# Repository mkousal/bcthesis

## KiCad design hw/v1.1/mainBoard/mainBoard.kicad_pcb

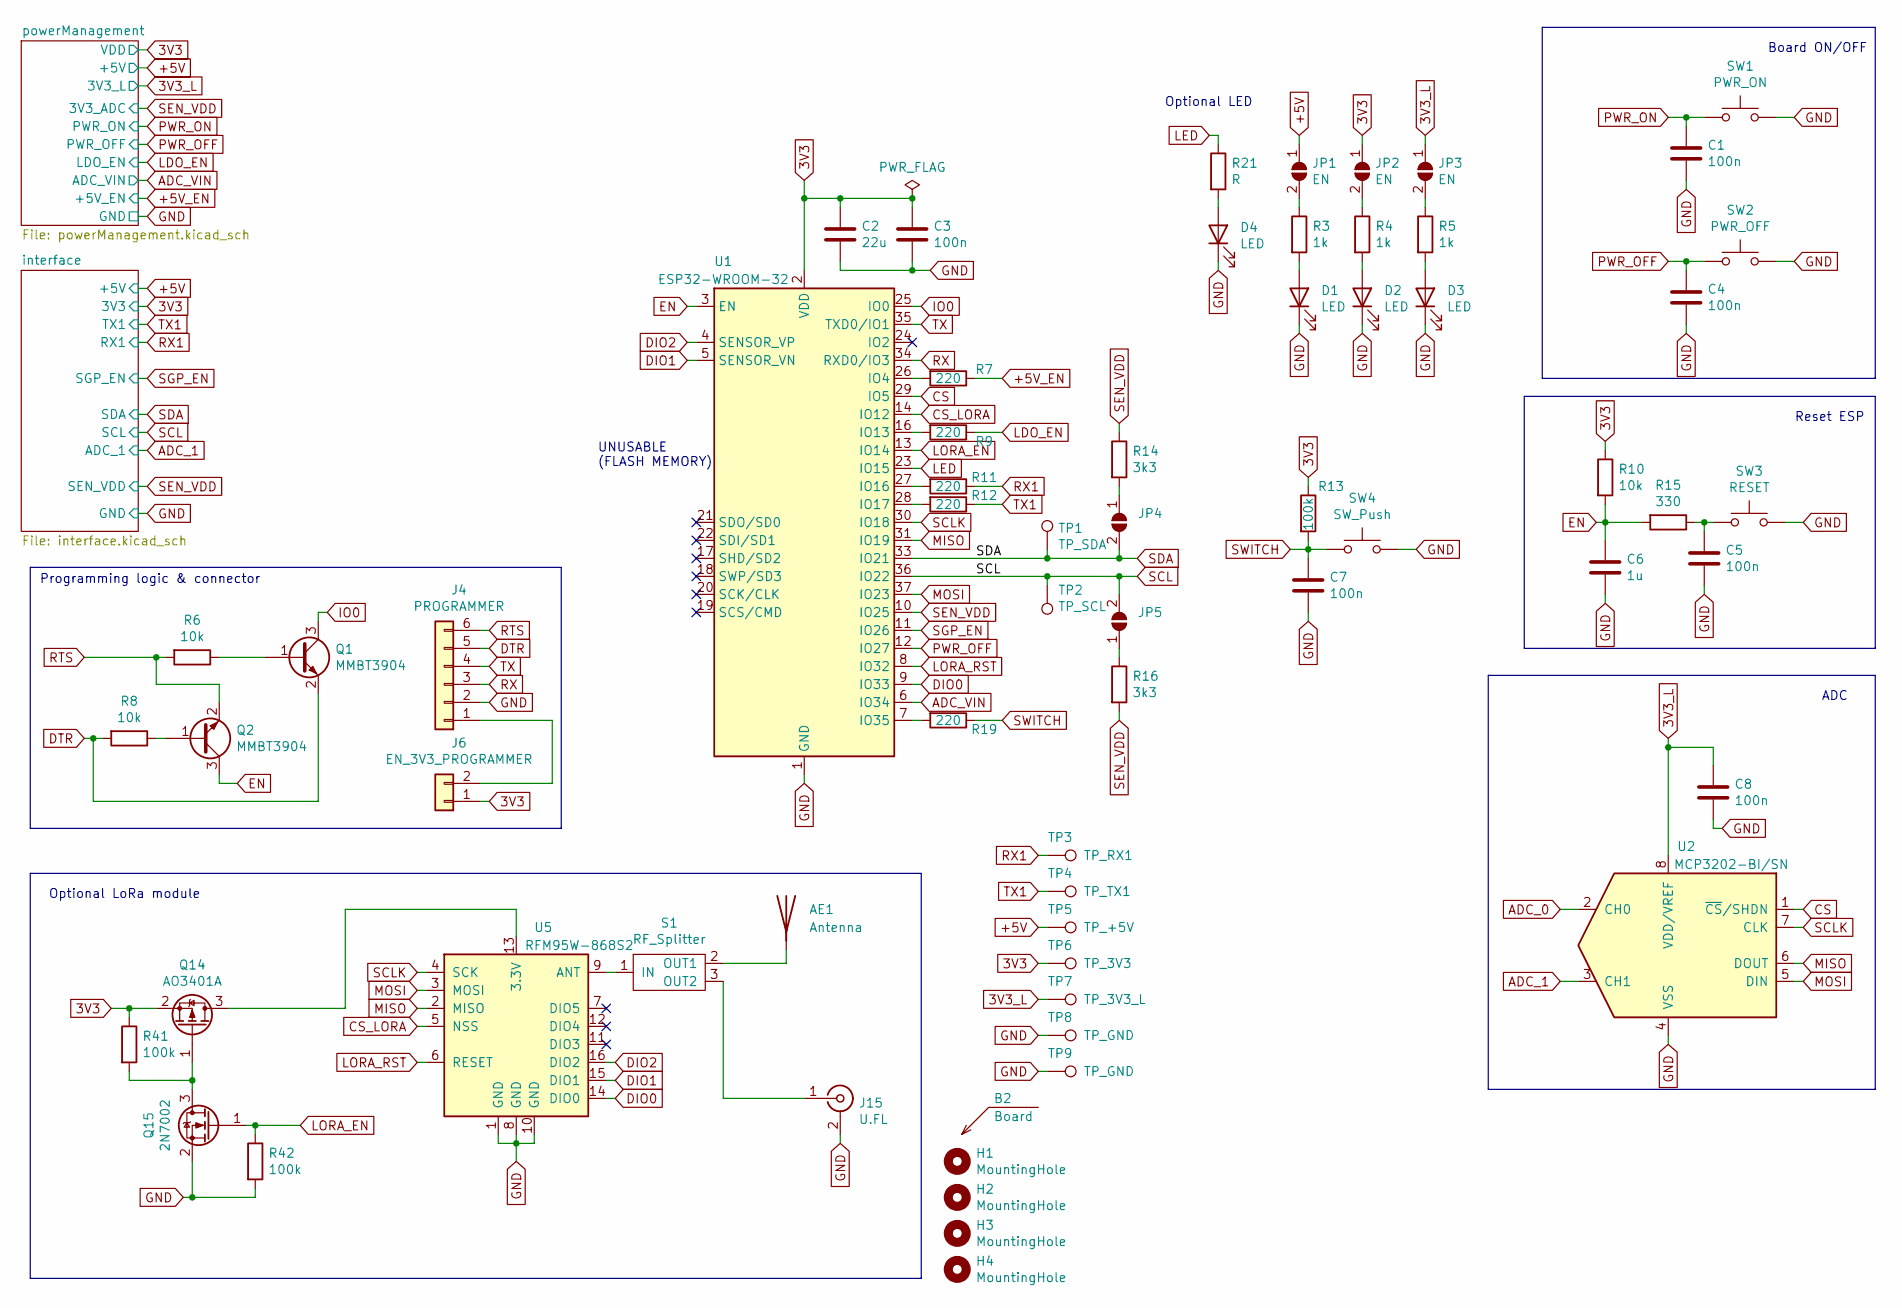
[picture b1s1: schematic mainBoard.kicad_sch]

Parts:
AE1: Antenna; ANT-868-CHP-T
B2: Board
C1, C3, C4, C5, C7, C8: 100n; C_0603_1608Metric; LCSC C1525
C2: 22u; C_0805_2012Metric; LCSC C45783
C6: 1u; C_0805_2012Metric; LCSC C52923
D1, D2, D3, D4: LED; LED_0805_2012Metric_Pad1.15x1.40mm_HandSolder
H1, H2, H3, H4: MountingHole; MountingHole_3.2mm_M3_Pad_Via
J4: PROGRAMMER; PinHeader_1x06_P2.54mm_Vertical
J6: EN_3V3_PROGRAMMER; PinHeader_1x02_P2.54mm_Vertical
J15: U.FL; U.FL_Hirose_U.FL-R-SMT-1_Vertical
JP1, JP2, JP3: EN; SolderJumper-2_P1.3mm_Open_RoundedPad1.0x1.5mm
JP4, JP5: SolderJumper-2_P1.3mm_Open_TrianglePad1.0x1.5mm
Q1, Q2: MMBT3904; SOT-23; LCSC C20526
Q14: AO3401A; SOT-23; LCSC C15127
Q15: 2N7002; SOT-23; LCSC C8545
R3, R4, R5: 1k; R_0805_2012Metric; LCSC C11702
R6, R8, R10: 10k; R_0805_2012Metric; LCSC C25744
R7, R9, R11, R12, R19: 220; R_0805_2012Metric; LCSC C25091
R13, R41, R42: 100k; R_0805_2012Metric; LCSC C25741
R14, R16: 3k3; R_0805_2012Metric; LCSC C25890
R15: 330; R_0805_2012Metric; LCSC C25104
R21: R; R_0805_2012Metric
S1: RF_Splitter
SW1: PWR_ON; SW_PUSH_6mm
SW2: PWR_OFF; SW_PUSH_6mm
SW3: RESET; SW_PUSH_6mm
SW4: SW_Push; SW_PUSH_6mm
TP1: TP_SDA; TestPoint_Pad_D1.5mm
TP2: TP_SCL; TestPoint_Pad_D1.5mm
TP3: TP_RX1; TestPoint_Pad_D1.5mm
TP4: TP_TX1; TestPoint_Pad_D1.5mm
TP5: TP_+5V; TestPoint_Pad_D1.5mm
TP6: TP_3V3; TestPoint_Pad_D1.5mm
TP7: TP_3V3_L; TestPoint_Pad_D1.5mm
TP8, TP9: TP_GND; TestPoint_Pad_D1.5mm
U1: ESP32-WROOM-32; LCSC C82899
U2: MCP3202-BI/SN; SOIC-8_3.9x4.9mm_P1.27mm
U5: RFM95W-868S2; HOPERF_RFM9XW_SMD

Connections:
3V3: C2.1, C3.1, J6.1, JP2.1 (A), Q14.2 (S), R10.1, R13.1, R41.1, TP6.1, U1.2 (VDD); also elsewhere on the board
3V3_L: C8.1, JP3.1 (A), TP7.1, U2.8 (VDD/VREF); also elsewhere on the board
+5V: JP1.1 (A), TP5.1; also elsewhere on the board
+5V_EN: R7.1; also elsewhere on the board
ADC_0: U2.2 (CH0)
ADC_1: U2.3 (CH1); also elsewhere on the board
ADC_VIN: U1.6 (IO34); also elsewhere on the board
CS: U1.29 (IO5), U2.1 (~CS/SHDN)
CS_LORA: U1.14 (IO12), U5.5 (NSS)
DIO0: U1.9 (IO33), U5.14 (DIO0)
DIO1: U1.5 (SENSOR_VN), U5.15 (DIO1)
DIO2: U1.4 (SENSOR_VP), U5.16 (DIO2)
DTR: J4.5, Q1.2 (E), R8.2
EN: C6.1, Q2.3 (C), R10.2, R15.2, U1.3 (EN)
GND: C1.2, C2.2, C3.2, C4.2, C5.2, C6.2, C7.2, C8.2, D1.1 (K), D2.1 (K), D3.1 (K), D4.1 (K), J4.2, J15.2 (Ext), Q15.2 (S), R42.2, SW1.2, SW2.2, SW3.2, SW4.2, TP8.1, TP9.1, U1.1 (GND), U1.15 (GND), U1.38 (GND), U1.39 (GND), U2.4 (VSS), U5.1 (GND), U5.8 (GND), U5.10 (GND); also elsewhere on the board
IO0: Q1.3 (C), U1.25 (IO0)
LDO_EN: R9.1; also elsewhere on the board
LED: R21.1, U1.23 (IO15)
LORA_EN: Q15.1 (G), R42.1, U1.13 (IO14)
LORA_RST: U1.8 (IO32), U5.6 (RESET)
MISO: U1.31 (IO19), U2.6 (DOUT), U5.2 (MISO)
MOSI: U1.37 (IO23), U2.5 (DIN), U5.3 (MOSI)
unnamed: AE1.1 (A), S1.2 (OUT1)
unnamed: C5.1, R15.1, SW3.1
unnamed: D1.2 (A), R3.2
unnamed: D2.2 (A), R4.2
unnamed: D3.2 (A), R5.2
unnamed: D4.2 (A), R21.2
unnamed: J4.1, J6.2
unnamed: J15.1 (In), S1.3 (OUT2)
unnamed: JP1.2 (B), R3.1
unnamed: JP2.2 (B), R4.1
unnamed: JP3.2 (B), R5.1
unnamed: JP4.1 (A), R14.2
unnamed: JP5.1 (A), R16.1
unnamed: Q1.1 (B), R6.1
unnamed: Q2.1 (B), R8.1
unnamed: Q14.1 (G), Q15.3 (D), R41.2
unnamed: Q14.3 (D), U5.13 (3.3V)
unnamed: R7.2, U1.26 (IO4)
unnamed: R9.2, U1.16 (IO13)
unnamed: R11.2, U1.27 (IO16)
unnamed: R12.2, U1.28 (IO17)
unnamed: R19.2, U1.7 (IO35)
unnamed: S1.1 (IN), U5.9 (ANT)
PWR_OFF: C4.1, SW2.1, U1.12 (IO27); also elsewhere on the board
PWR_ON: C1.1, SW1.1; also elsewhere on the board
RTS: J4.6, Q2.2 (E), R6.2
RX: J4.3, U1.34 (RXD0/IO3)
RX1: R11.1, TP3.1; also elsewhere on the board
SCL: JP5.2 (B), TP2.1, U1.36 (IO22); also elsewhere on the board
SCLK: U1.30 (IO18), U2.7 (CLK), U5.4 (SCK)
SDA: JP4.2 (B), TP1.1, U1.33 (IO21); also elsewhere on the board
SEN_VDD: R14.1, R16.2, U1.10 (IO25); also elsewhere on the board
SGP_EN: U1.11 (IO26); also elsewhere on the board
SWITCH: C7.1, R13.2, R19.1, SW4.1
TX: J4.4, U1.35 (TXD0/IO1)
TX1: R12.1, TP4.1; also elsewhere on the board

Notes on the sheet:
ADC
Programming logic & connector
Reset ESP
Optional LoRa module
UNUSABLE (FLASH MEMORY)
Board ON/OFF
Optional LED

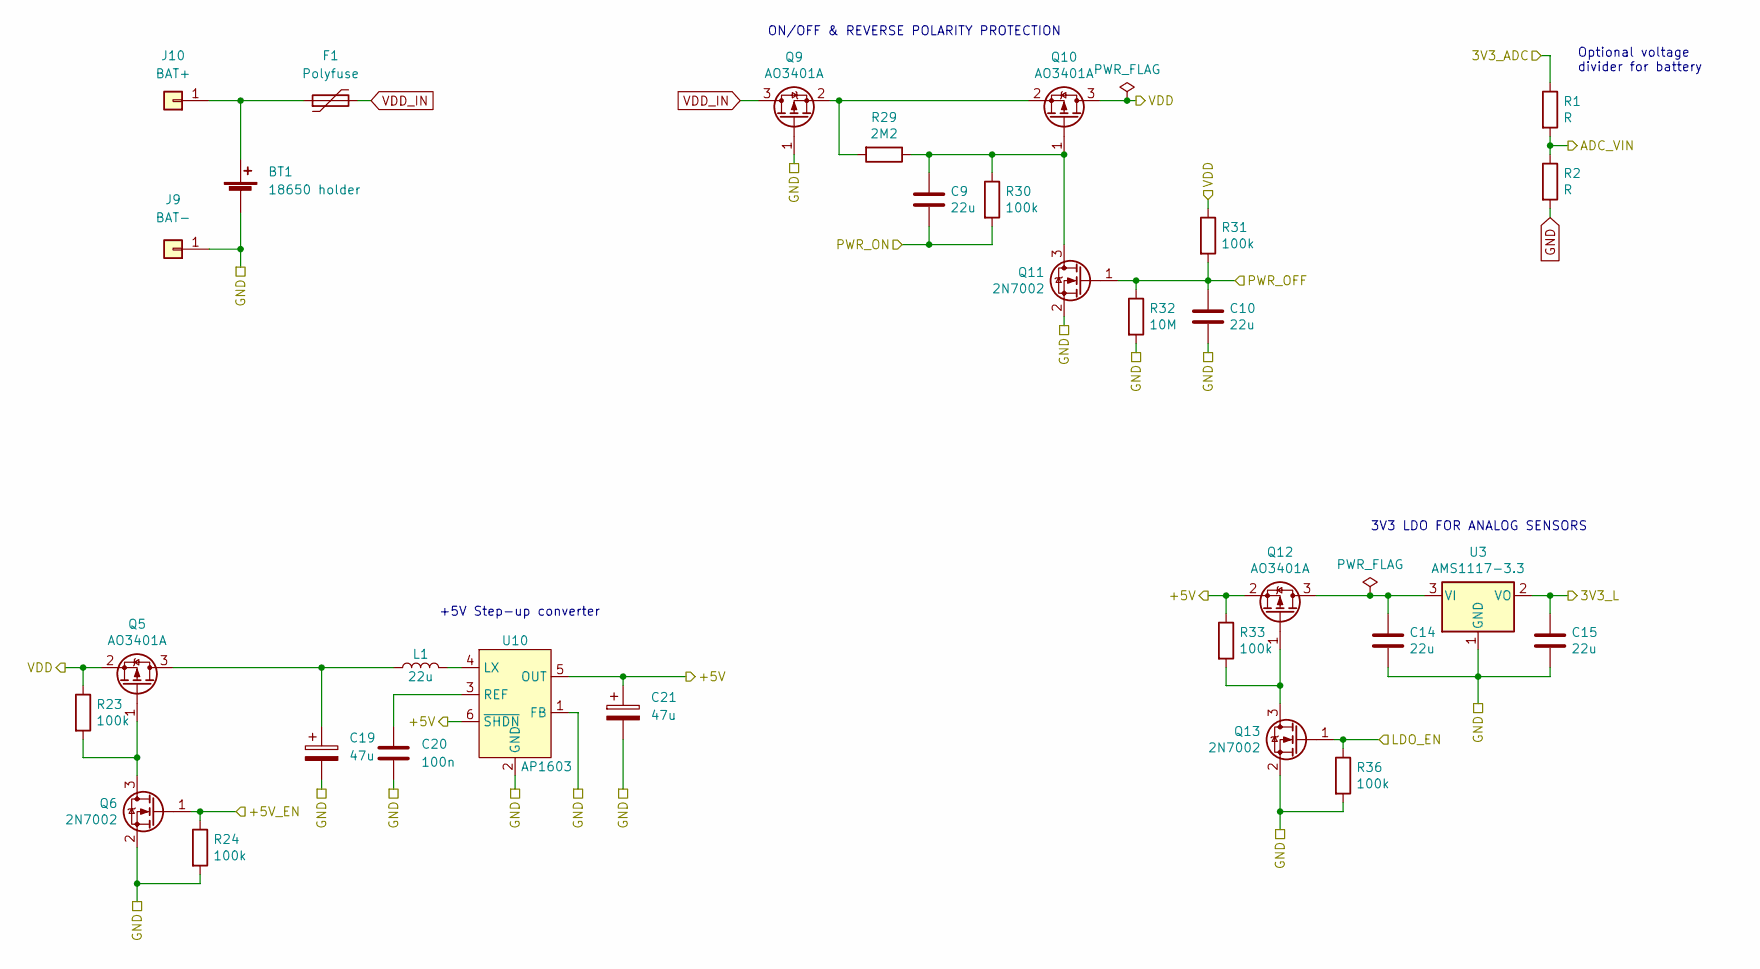
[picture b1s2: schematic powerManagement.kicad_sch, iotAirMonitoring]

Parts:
BT1: 18650 holder; JST_XH_B2B-XH-A_1x02_P2.50mm_Vertical
C9, C10, C14, C15: 22u; C_0805_2012Metric; LCSC C45783
C19, C21: 47u; CP_Elec_6.3x7.7
C20: 100n; C_0603_1608Metric
F1: Polyfuse; Fuse_1812_4532Metric_Pad1.30x3.40mm_HandSolder
J9: BAT-; 2mm_Banana-Socket
J10: BAT+; 2mm_Banana-Socket
L1: 22u; L_Coilcraft_LPS4018
Q5, Q9, Q10, Q12: AO3401A; SOT-23; LCSC C15127
Q6, Q11, Q13: 2N7002; SOT-23; LCSC C8545
R1, R2: R; R_0805_2012Metric_Pad1.20x1.40mm_HandSolder
R23, R24, R30, R33, R36: 100k; R_0805_2012Metric; LCSC C25741
R29: 2M2; R_0805_2012Metric; LCSC C25741
R31: 100k; R_0805_2012Metric; LCSC C25744
R32: 10M; R_0805_2012Metric; LCSC C25741
U3: AMS1117-3.3; SOT-223-3_TabPin2; LCSC C6186
U10: AP1603; SOT-23-6_Handsoldering

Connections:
3V3: Q5.2 (S), Q10.3 (D), R23.1, R31.1; also elsewhere on the board
3V3_L: C15.1, U3.2 (VO); also elsewhere on the board
+5V: C21.1, Q12.2 (S), R33.1, U10.5 (OUT), U10.6 (~SHDN); also elsewhere on the board
+5V_EN: Q6.1 (G), R24.1; also elsewhere on the board
ADC_VIN: R1.2, R2.1; also elsewhere on the board
GND: BT1.2 (-), C10.2, C14.2, C15.2, C19.2, C20.2, C21.2, J9.1, Q6.2 (S), Q9.1 (G), Q11.2 (S), Q13.2 (S), R2.2, R24.2, R32.2, R36.2, U3.1 (GND), U10.1 (FB), U10.2 (GND); also elsewhere on the board
LDO_EN: Q13.1 (G), R36.1; also elsewhere on the board
unnamed: BT1.1 (+), F1.1, J10.1
unnamed: C9.1, Q10.1 (G), Q11.3 (D), R29.1, R30.1
unnamed: C14.1, Q12.3 (D), U3.3 (VI)
unnamed: C19.1, L1.1, Q5.3 (D)
unnamed: C20.1, U10.3 (REF)
unnamed: L1.2, U10.4 (LX)
unnamed: Q5.1 (G), Q6.3 (D), R23.2
unnamed: Q9.2 (S), Q10.2 (S), R29.2
unnamed: Q12.1 (G), Q13.3 (D), R33.2
PWR_OFF: C10.1, Q11.1 (G), R31.2, R32.1; also elsewhere on the board
PWR_ON: C9.2, R30.2; also elsewhere on the board
SEN_VDD: R1.1; also elsewhere on the board
VDD_IN: F1.2, Q9.3 (D)

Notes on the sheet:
Optional voltage divider for battery
+5V Step-up converter
ON/OFF & REVERSE POLARITY PROTECTION
3V3 LDO FOR ANALOG SENSORS

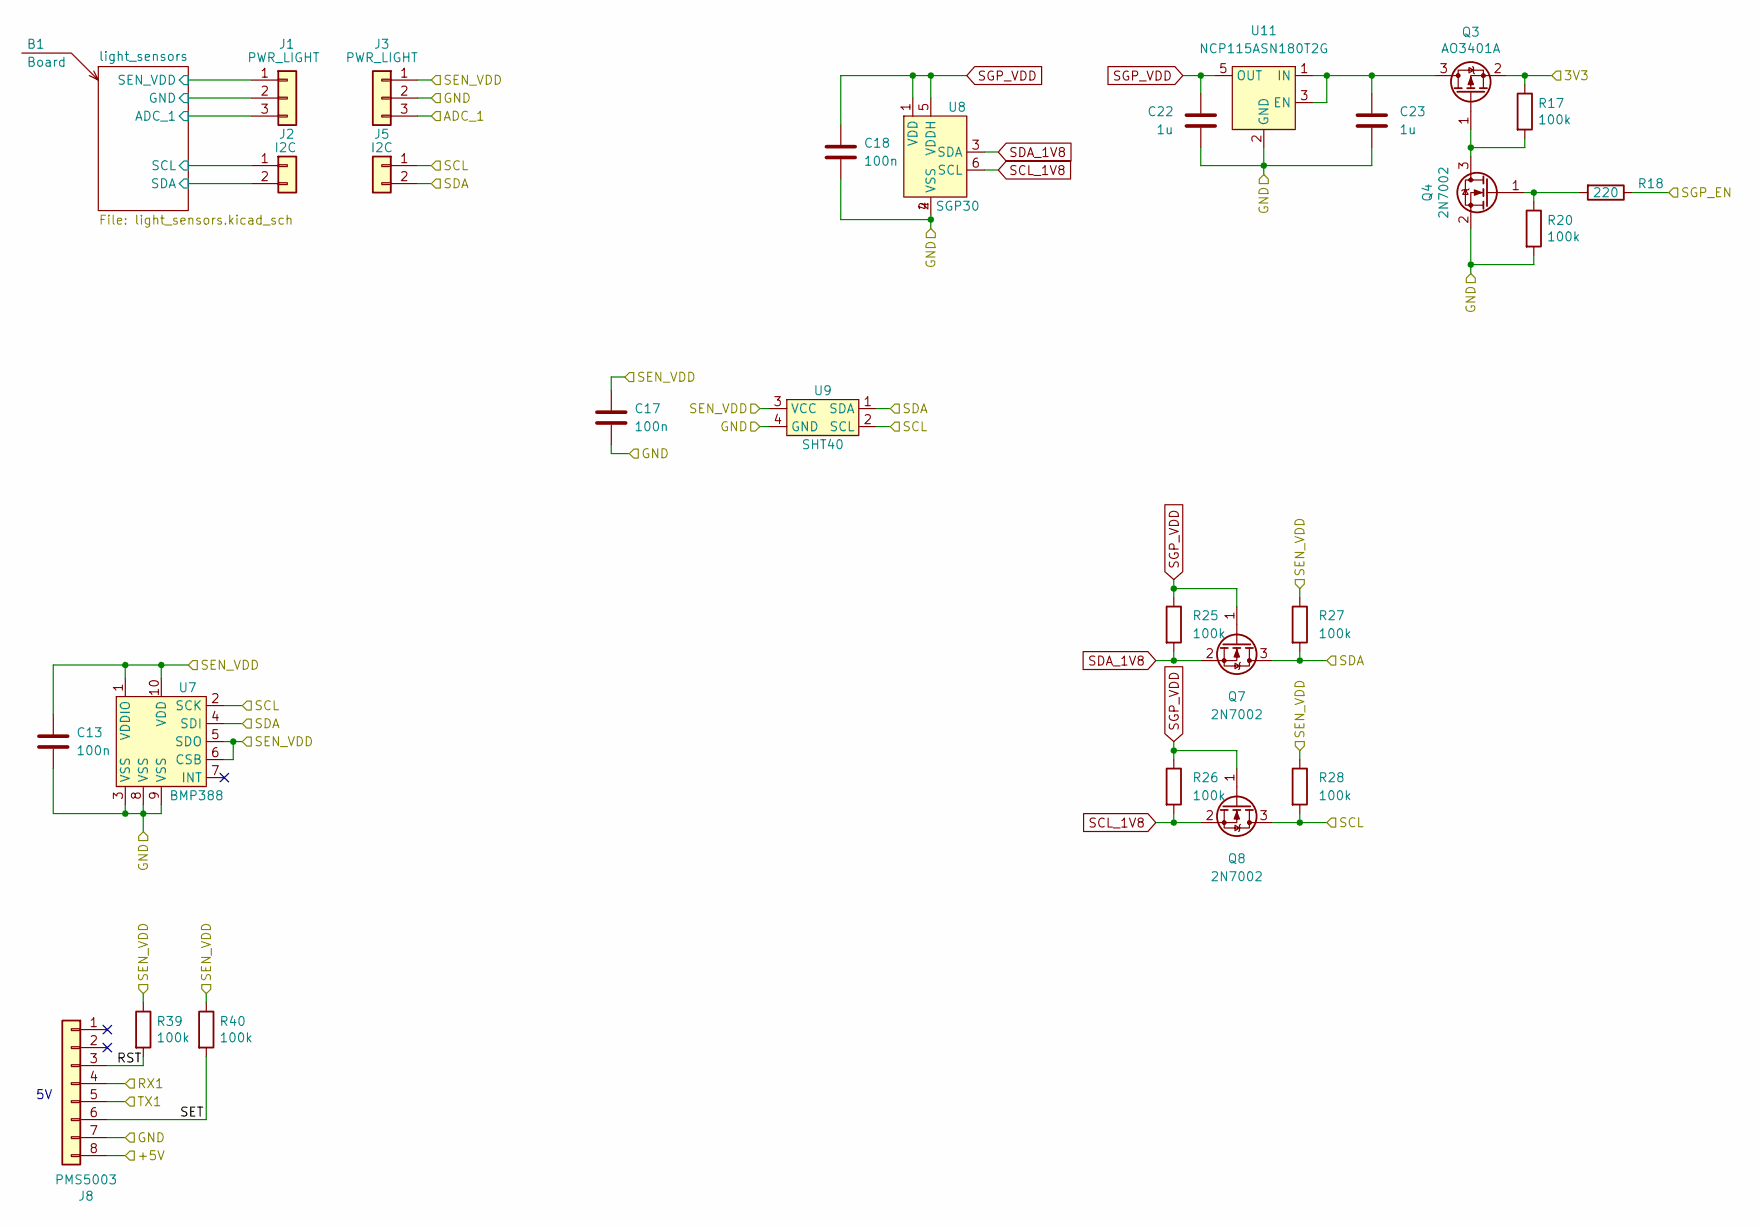
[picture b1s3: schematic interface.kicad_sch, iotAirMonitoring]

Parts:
B1: Board
C13, C17, C18: 100n; C_0603_1608Metric
C22, C23: 1u; C_0805_2012Metric
J1: PWR_LIGHT; PinHeader_1x03_P2.54mm_Vertical
J2: I2C; PinHeader_1x02_P2.54mm_Vertical
J3: PWR_LIGHT; PinSocket_1x03_P2.54mm_Vertical
J5: I2C; PinSocket_1x02_P2.54mm_Vertical
J8: PMS5003; Molex_PicoBlade_53048-0810_1x08_P1.25mm_Horizontal
Q3: AO3401A; SOT-23; LCSC C15127
Q4: 2N7002; SOT-23; LCSC C8545
Q7, Q8: 2N7002; SOT-23
R17, R20, R39, R40: 100k; R_0805_2012Metric; LCSC C25741
R18: 220; R_0805_2012Metric; LCSC C25091
R25, R26, R27, R28: 100k; R_0805_2012Metric
U7: BMP388
U8: SGP30
U9: SHT40
U11: NCP115ASN180T2G; TSOP-5_1.65x3.05mm_P0.95mm

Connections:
3V3: Q3.2 (S), R17.1; also elsewhere on the board
+5V: J8.8; also elsewhere on the board
/interface/RST: J8.3, R39.2
/interface/SET: J8.6, R40.2
/interface/light_sensors/ADC_1: J1.3; also elsewhere on the board
/interface/light_sensors/GND: J1.2; also elsewhere on the board
/interface/light_sensors/SCL: J2.1; also elsewhere on the board
/interface/light_sensors/SDA: J2.2; also elsewhere on the board
/interface/light_sensors/SEN_VDD: J1.1; also elsewhere on the board
ADC_1: J3.3; also elsewhere on the board
GND: C13.2, C17.2, C18.2, C22.2, C23.2, J3.2, J8.7, Q4.2 (S), R20.2, U7.3 (VSS), U7.8 (VSS), U7.9 (VSS), U8.2 (VSS), U8.4, U9.4 (GND), U11.2 (GND); also elsewhere on the board
unnamed: C23.1, Q3.3 (D), U11.1 (IN), U11.3 (EN)
unnamed: Q3.1 (G), Q4.3 (D), R17.2
unnamed: Q4.1 (G), R18.2, R20.1
RX1: J8.4; also elsewhere on the board
SCL: J5.1, Q8.3 (D), R28.2, U7.2 (SCK), U9.2 (SCL); also elsewhere on the board
SCL_1V8: Q8.2 (S), R26.2, U8.6 (SCL)
SDA: J5.2, Q7.3 (D), R27.2, U7.4 (SDI), U9.1 (SDA); also elsewhere on the board
SDA_1V8: Q7.2 (S), R25.2, U8.3 (SDA)
SEN_VDD: C13.1, C17.1, J3.1, R27.1, R28.1, R39.1, R40.1, U7.1 (VDDIO), U7.5 (SDO), U7.6 (CSB), U7.10 (VDD), U9.3 (VCC); also elsewhere on the board
SGP_EN: R18.1; also elsewhere on the board
SGP_VDD: C18.1, C22.1, Q7.1 (G), Q8.1 (G), R25.1, R26.1, U8.1 (VDD), U8.5 (VDDH), U11.5 (OUT)
TX1: J8.5; also elsewhere on the board

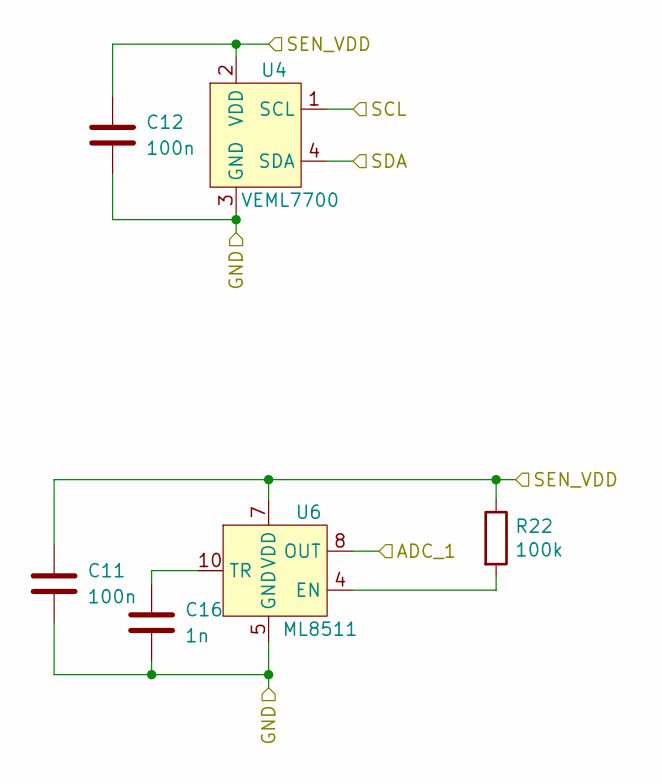
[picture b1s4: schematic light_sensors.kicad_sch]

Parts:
C11, C12: 100n; C_0603_1608Metric
C16: 1n; C_0805_2012Metric
R22: 100k; R_0805_2012Metric; LCSC C25741
U4: VEML7700
U6: ML8511

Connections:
/interface/light_sensors/ADC_1: U6.8 (OUT); also elsewhere on the board
/interface/light_sensors/GND: C11.2, C12.2, C16.2, U4.3 (GND), U6.5 (GND); also elsewhere on the board
/interface/light_sensors/SCL: U4.1 (SCL); also elsewhere on the board
/interface/light_sensors/SDA: U4.4 (SDA); also elsewhere on the board
/interface/light_sensors/SEN_VDD: C11.1, C12.1, R22.1, U4.2 (VDD), U6.7 (VDD); also elsewhere on the board
unnamed: C16.1, U6.10 (TR)
unnamed: R22.2, U6.4 (EN)

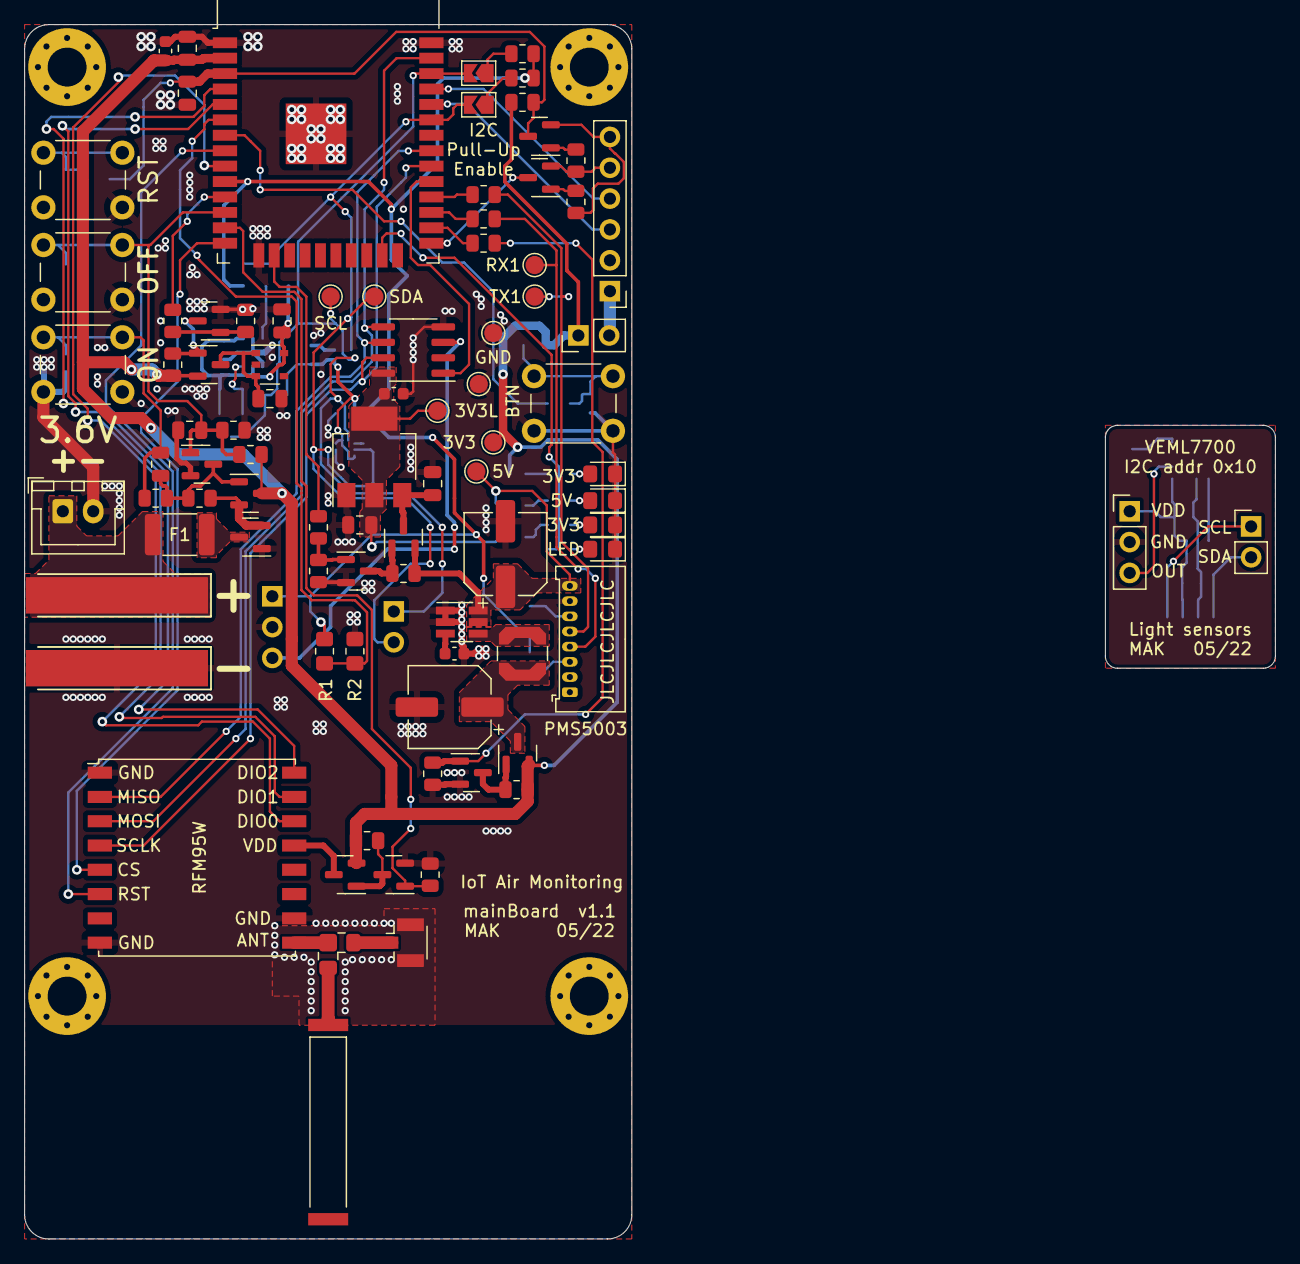
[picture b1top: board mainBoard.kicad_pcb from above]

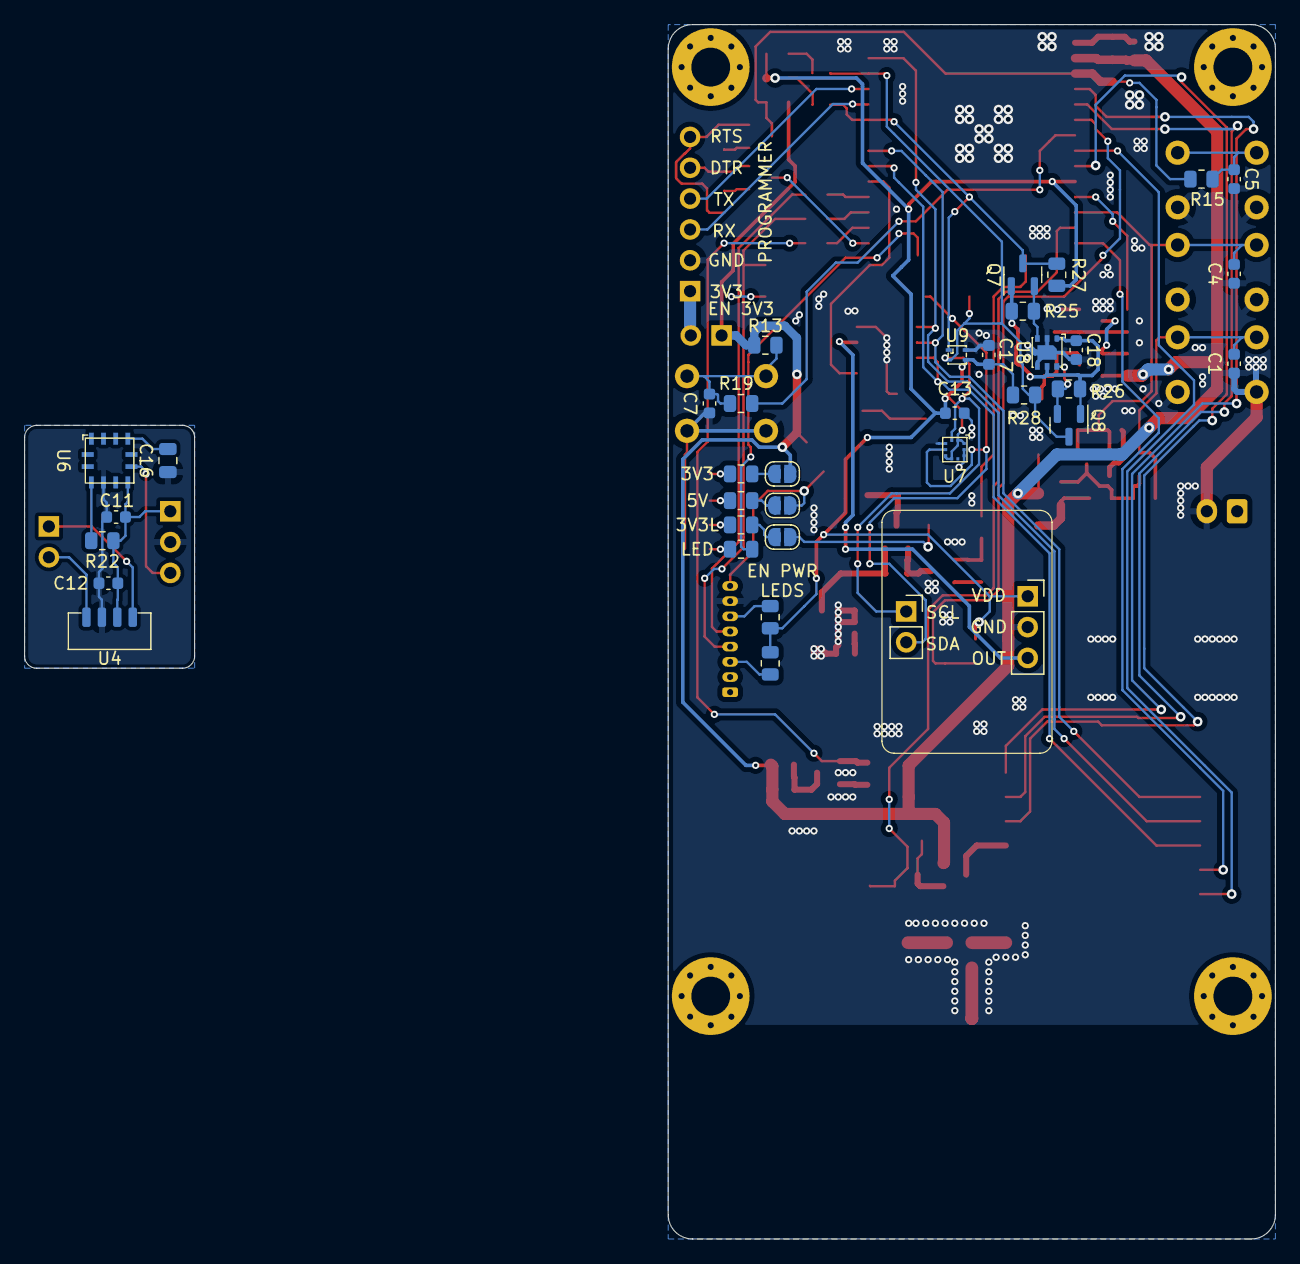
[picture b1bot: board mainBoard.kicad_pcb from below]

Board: 2 copper layers, 103.0 x 100.0 mm, 130 parts (36 on the bottom side), 82 nets.

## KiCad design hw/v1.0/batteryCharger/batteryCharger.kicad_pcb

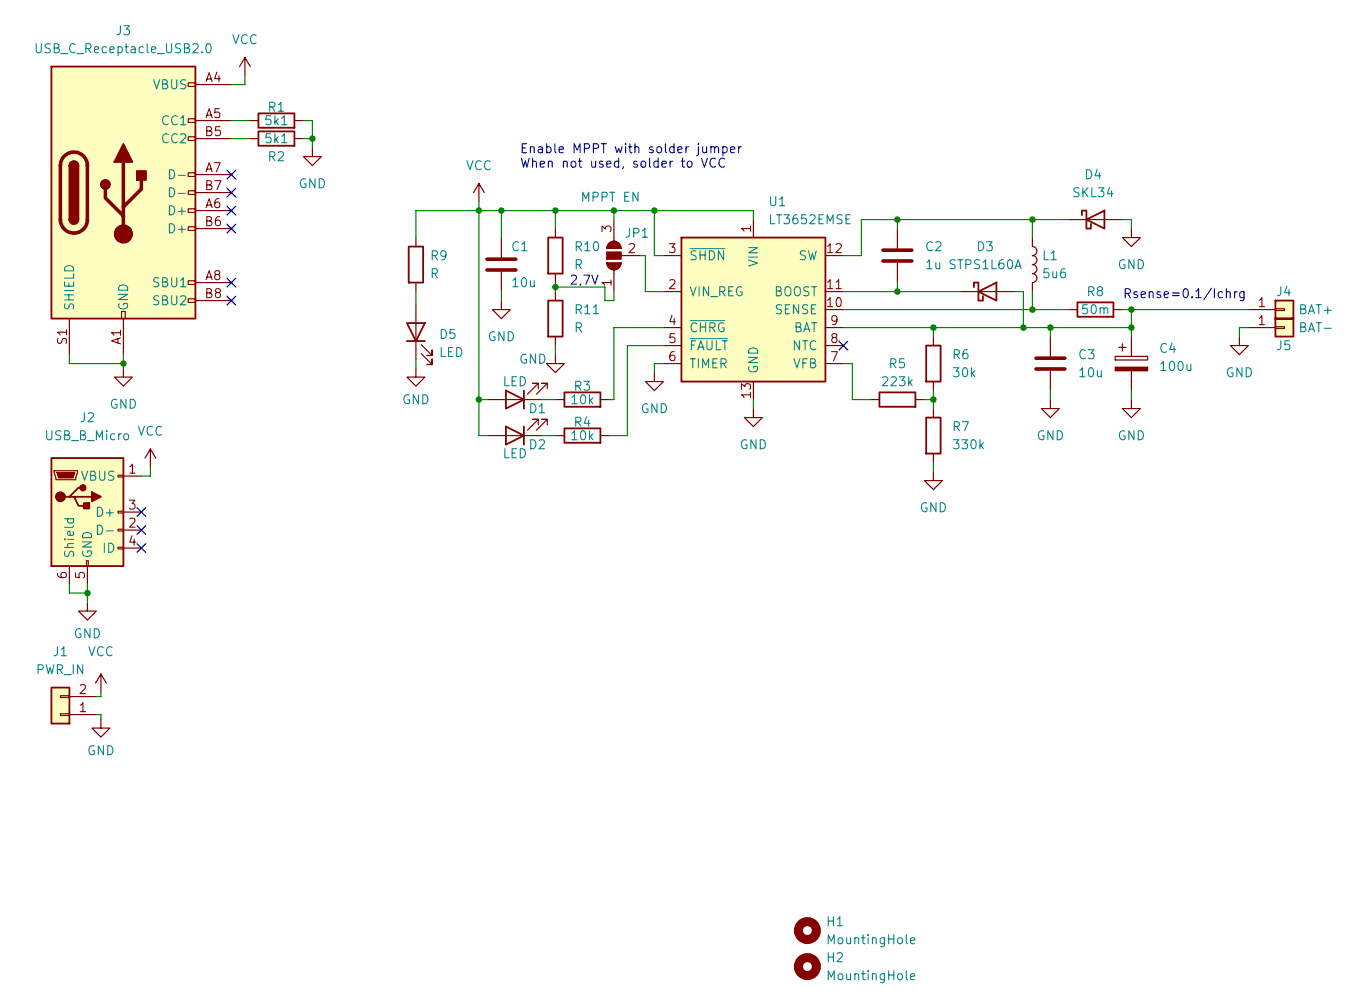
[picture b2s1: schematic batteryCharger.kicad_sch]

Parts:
C1, C3: 10u; C_0805_2012Metric_Pad1.18x1.45mm_HandSolder
C2: 1u; C_0805_2012Metric_Pad1.18x1.45mm_HandSolder
C4: 100u; CP_Radial_D6.3mm_P2.50mm
D1, D2, D5: LED; LED_0805_2012Metric_Pad1.15x1.40mm_HandSolder
D3: STPS1L60A; D_SMA_Handsoldering
D4: SKL34; D_SOD-123F
H1, H2: MountingHole; MountingHole_3.2mm_M3_Pad_Via
J1: PWR_IN; PinHeader_1x02_P2.54mm_Vertical
J2: USB_B_Micro; USB_Micro-B_Amphenol_10118194_Horizontal
J3: USB_C_Receptacle_USB2.0; USB_C_Receptacle_HRO_TYPE-C-31-M-12
J4: BAT+; 2mm_Banana-Plug
J5: BAT-; 2mm_Banana-Plug
JP1: MPPT EN; SolderJumper-3_P1.3mm_Open_RoundedPad1.0x1.5mm_NumberLabels
L1: 5u6; L_12x12mm_H8mm
R1, R2: 5k1; R_0805_2012Metric_Pad1.20x1.40mm_HandSolder
R3, R4: 10k; R_0805_2012Metric_Pad1.20x1.40mm_HandSolder
R5: 223k; R_0805_2012Metric_Pad1.20x1.40mm_HandSolder
R6: 30k; R_0805_2012Metric_Pad1.20x1.40mm_HandSolder
R7: 330k; R_0805_2012Metric_Pad1.20x1.40mm_HandSolder
R8: 50m; R_1206_3216Metric_Pad1.30x1.75mm_HandSolder
R9, R10, R11: R; R_0805_2012Metric_Pad1.20x1.40mm_HandSolder
U1: LT3652EMSE; MSOP-12-1EP_3x4mm_P0.65mm_EP1.65x2.85mm

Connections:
GND: C1.2, C3.2, C4.2, D4.2 (A), D5.1 (K), J1.1, J2.5 (GND), J2.6 (Shield), J3.A1 (GND), J3.A12 (GND), J3.B1 (GND), J3.B12 (GND), J3.S1 (SHIELD), J5.1, R1.2, R2.2, R7.2, R11.2, U1.6 (TIMER), U1.13 (GND)
unnamed: C2.1, D4.1 (K), L1.1, U1.12 (SW)
unnamed: C2.2, D3.1 (K), U1.11 (BOOST)
unnamed: C3.1, C4.1, D3.2 (A), J4.1, R6.1, R8.2, U1.9 (BAT)
unnamed: D1.1 (K), R3.1
unnamed: D2.1 (K), R4.1
unnamed: D5.2 (A), R9.2
unnamed: J3.A5 (CC1), R1.1
unnamed: J3.B5 (CC2), R2.1
unnamed: JP1.1 (A), R10.2, R11.1
unnamed: JP1.2 (C), U1.2 (VIN_REG)
unnamed: L1.2, R8.1, U1.10 (SENSE)
unnamed: R3.2, U1.4 (~CHRG)
unnamed: R4.2, U1.5 (~FAULT)
unnamed: R5.1, U1.7 (VFB)
unnamed: R5.2, R6.2, R7.1
VCC: C1.1, D1.2 (A), D2.2 (A), J1.2, J2.1 (VBUS), J3.A4 (VBUS), J3.A9 (VBUS), J3.B4 (VBUS), J3.B9 (VBUS), JP1.3 (B), R9.1, R10.1, U1.1 (VIN), U1.3 (~SHDN)

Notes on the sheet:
Rsense=0.1/Ichrg
2,7V
Enable MPPT with solder jumper When not used, solder to VCC

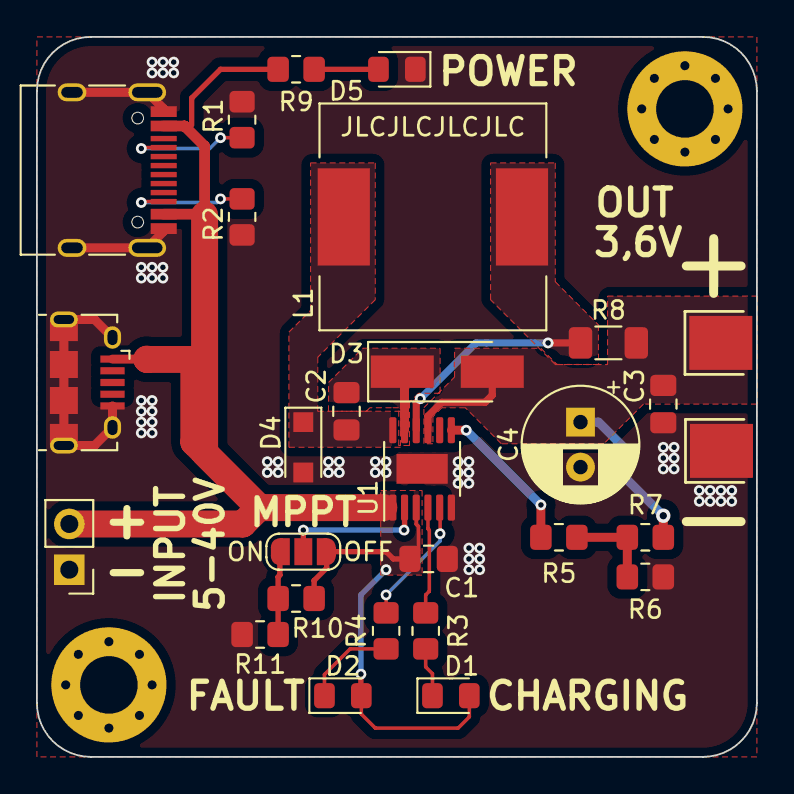
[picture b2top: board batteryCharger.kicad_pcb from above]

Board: 2 copper layers, 40.0 x 40.0 mm, 30 parts (0 on the bottom side), 17 nets.

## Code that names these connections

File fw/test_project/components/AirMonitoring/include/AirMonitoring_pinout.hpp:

/**
 * @file AirMonitoring_pinout.hpp
 * @author Martin Kousal ()
 * @brief Pinout defines for Air monitoring main board
 * @version 0.1
 * @date 2022-04-07
 * 
 * @copyright Copyright (c) 2022
 * 
 */

#pragma once

#include <driver/gpio.h>
#include <driver/adc.h>

namespace Am {

static const gpio_num_t IO0 = GPIO_NUM_0;
static const gpio_num_t IO2 = GPIO_NUM_2;
static const gpio_num_t IO12 = GPIO_NUM_12;
static const gpio_num_t IO4 = GPIO_NUM_4;
static const gpio_num_t IO5 = GPIO_NUM_5;
static const gpio_num_t IO13 = GPIO_NUM_13;
static const gpio_num_t IO14 = GPIO_NUM_14;
static const gpio_num_t IO15 = GPIO_NUM_15;
static const gpio_num_t IO16 = GPIO_NUM_16;
static const gpio_num_t IO17 = GPIO_NUM_17;
static const gpio_num_t IO18 = GPIO_NUM_18;
static const gpio_num_t IO19 = GPIO_NUM_19;
static const gpio_num_t IO21 = GPIO_NUM_21;
static const gpio_num_t IO25 = GPIO_NUM_25;
static const gpio_num_t IO26 = GPIO_NUM_26;
static const gpio_num_t IO27 = GPIO_NUM_27;
static const gpio_num_t IO32 = GPIO_NUM_32;
static const gpio_num_t IO33 = GPIO_NUM_33;
static const gpio_num_t IO34 = GPIO_NUM_34;
static const gpio_num_t IO35 = GPIO_NUM_35;
static const gpio_num_t IO23 = GPIO_NUM_23;

static const gpio_num_t PMS_EN = IO4;
static const gpio_num_t CS = IO5;
static const gpio_num_t CS_LORA = IO12;
static const gpio_num_t LDO_EN = IO13;
static const gpio_num_t LORA_EN = IO14;
static const gpio_num_t LED = IO15;
static const gpio_num_t RX1 = IO16;
static const gpio_num_t TX1 = IO17;
static const gpio_num_t SCLK = IO18;
static const gpio_num_t MISO = IO19;
static const gpio_num_t MOSI = IO23;
static const gpio_num_t SEN_VDD_EN = IO25;
static const gpio_num_t SGP_EN = IO26;
static const gpio_num_t POWER_OFF = IO27;
static const gpio_num_t LORA_RST = IO32;
static const gpio_num_t DIO0 = IO33;
static const gpio_num_t DIO1 = GPIO_NUM_39;
// static const gpio_num_t IO34 = ADC_VIN;
static const gpio_num_t SWITCH = IO35;

static const gpio_num_t I2C_MASTER_SDA = GPIO_NUM_21;
static const gpio_num_t I2C_MASTER_SCL = GPIO_NUM_22;

static const adc_unit_t BATT_ADC_UNIT = ADC_UNIT_1;
static const adc1_channel_t BATT_ADC_CHANNEL = ADC1_CHANNEL_6;

} // namespace Am

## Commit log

2021-10-13 Import BUT LaTex template
2021-10-25 Made some changes in settings of latex template
2021-10-25 Create KiCad project
2021-10-25 Add on/off and reverse polarity protection circuit, start draw step-down
2021-10-25 Finish stepdown schematic
2021-10-26 Add LDO regulator and ESP32
2021-10-27 More work on schematic
2021-10-28 Add way more parts to schematic
2021-10-29 Schematic nearly finished
2021-10-29 Nearly finished schematic, add optional LoRa module
2021-10-30 Start routing main board
2021-10-31 More component placement
2021-11-01 Nearly finished component placement
2021-11-01 Start routing of main board
2021-11-01 More routing on main board
2021-11-02 First version routed main board
2021-11-02 Add TestPads, improve silkscreen
2021-11-02 Create Makefile for gerbers generation, type in missing LCSC codes
2021-11-02 Add Makefile file
2021-11-03 Add JLCPCB assembly correction, generate gerber data
2021-11-07 Update settings of latex template
2021-11-14 Add generated PDF from BUT system, write some text
2021-11-14 Write carbon monoxide and particulate matter measurement sections
2021-11-15 Write light intensity and UV light intensity section
2021-11-15 Start temperature section
2021-11-17 Add more sections
2021-11-18 Add more text
2021-11-18 Create new branch, add testing firmware
2021-11-18 Added czech citation file and more text
2021-11-19 Add humidity measuring text, citation to image, fix some nbsp
2021-11-19 Replace white characters with nbsp
2021-11-19 Add more theoretical text, include new bibliography package (maybe properly) reflecting ISO 690 format
2021-11-20 Add text about IoT networks
2021-11-20 Maybe finished theoretical part of text
2021-11-20 Add first type of sensor
2021-11-20 Add reference to table in chapter with dust sensors
2021-11-20 Add dust sensor selection text
2021-11-21 Add image of PMS5003 sensor and add sources reference
2021-11-29 Add section sensor of carbon monoxide
2021-11-30 Add UV sensor selection section
2021-12-01 Add temperature sensor choice chapter and sources
2021-12-05 Add section with final selection of temperature sensor and its image
2021-12-06 Add section with light intensity sensor selection
2021-12-07 Add some text to section about selecting atmospheric pressure sensor
2021-12-07 Add text section with selecting air pressure and humidity sensor
2021-12-07 Replace white spaces with nbsp
2021-12-13 Replace pdf generated from BUT system, fix citation dates and image centering
2021-12-13 Add microcontroler selection section
2021-12-14 Add more text into MCU selection section
2021-12-14 Fix typos, add power supply requirement to MCU selection section
2021-12-15 Add more text and resources
2021-12-15 Remove blank pages
2021-12-16 Add block schematic to introduction section, add ADC section and LoRa module selection section
2021-12-16 Add WiFi section
2021-12-17 Add text section with power supplies
2021-12-18 Add step-down section
2021-12-18 Add stepdown schematic
2021-12-18 Add linear voltage regulator section
2021-12-18 Add more text to schematics section, add full block schematics
2021-12-18 Add PCB making section
2021-12-19 Fix typos, add data server choice chapter
2021-12-19 Finish data servers section
2021-12-19 Add end chapter
2021-12-19 Add photos, fix typos, add abstract and so on
2021-12-19 Fix bibliography url overflow
2021-12-19 Fix typos
2021-12-29 Add image of UV light spectrum
2021-12-29 Make some tests
2021-12-29 Fix typos, move some pictures and tables
2022-01-02 Replace pdf from IS BUT
2022-01-02 Add resources
2022-01-02 Fix some details in text
2022-01-02 Fix typos, ready for submit
2022-01-03 Start work at presentation
2022-01-03 Maybe finish presentation
2022-01-03 Fix typos in presentation
2022-01-04 Replaced logo in presentation, fix some text
2022-01-04 Add some presentation enhancement
2022-01-17 Move whole project to C++, rewrite complete code using classes, working SHT40 communication
2022-01-18 Add prototype of veml7700 library
2022-01-20 Working light sensor library
2022-01-25 First prototype of BMP lib
2022-01-26 Working pms sensor
2022-01-30 Read calibration data from BMP388, make some adjustment to I2C driver, use thread in main program
2022-01-30 Repair pressure measurement
2022-01-31 Working relative pressure calculation with compensation
2022-02-08 Working dust, temp, humidity, light, pressure
2022-02-09 First prototype of SPI library
2022-02-11 Working UV measurement
2022-02-11 Add more print info from PMS sensor, fix typo in mcp sensor
2022-02-11 Restructuralise project, make component and separate .cpp and .hpp files
2022-02-15 Moved HW v0.1 project files
2022-02-15 Move latex .gitignore, which was causing problems in folder name with dot
2022-02-15 Start work at batteryCharger
2022-02-17 Routing charger
2022-02-17 Finish routing chargerBoard
2022-02-20 Add packages, start making v1.0
2022-02-21 Create sensor footprints and symbols
2022-02-27 Start routing PCB
2022-03-01 More component placement in mainboard
2022-03-02 Maybe final component placement
2022-03-02 Start routing mainBoard
2022-03-03 More routing at mainBoard
2022-03-03 Maybe finished first component placement and routing mainBoard
2022-03-04 Tweak silkscreen at mainBoard, add MPPT option to batteryCharger
2022-03-04 Finished v1.0, mainBoard, batteryCharger
2022-03-16 Finish sending data over WiFi with MQTT protocol
2022-03-27 Fix typos in text, replace PDF file from BUT system
2022-03-28 New PDF
2022-03-31 Updated text
2022-04-03 Working SGP30 measuring and sending to server
2022-04-04 Improved deep sleep current consumption
2022-04-06 Cleanup main code
2022-04-07 Add some pins to deep sleep isolation, start working on doxygen documentation
2022-04-07 More progress at documentation, cleanup code
2022-04-07 First try build doxygen documentation with github actions
2022-04-07 First version of doxyfile
2022-04-07 Add LoRaWAN TTN component and run menuconfig to prepare it
2022-04-11 Try connecting to TTN via LoRaWAN
2022-04-11 Working sending data to TTN via LoRaWAN
2022-04-13 Reworked checking completed tasks, cleanup code
2022-04-15 Cosmetic code changes
2022-04-16 Add battery voltage measurement
2022-04-18 Fix SHT40 read issue
2022-04-22 Fix issue with connecting to TTN after deepsleep, improve battery voltage reading and power off device when low voltage
2022-04-25 Move definitions from CMakeLists to one main file
2022-04-30 Work at selecting carbon dioxide sensor
2022-05-09 Created HW mainBoard v1.1, fix mirrored footprint, RFM95W to SMD fotprint, silkscreen and add sensor board with light sensors
2022-05-10 Add power section to text
2022-05-16 Fixed powering device off when low voltage
2022-05-16 Fix mistakes from consultation
2022-05-17 Added step-up section and schematics, switched to bachelor instead of semestral work, fix some mistakes
2022-05-17 Replaced title page with bachelor one
2022-05-18 Add LDO selection section
2022-05-18 Replaced final block schematic
2022-05-18 Add text to final conencting of device
2022-05-19 Add battery charger section
2022-05-19 Finish batteryCharger text section, add schematics into it
2022-05-21 Add PCB making up section
2022-05-21 Add mainBoard creation section
2022-05-22 Add PCB renders from KiCad
2022-05-22 Make links clickable
2022-05-22 Add flowchart, more software text
2022-05-22 Add more software text
2022-05-22 Renamed fw folder
2022-05-22 Make code clean, move definitions
2022-05-22 Maybe move all definitions to one file
2022-05-22 Add device configuring for TTN
2022-05-22 fw: Add MQTT topic definition
2022-05-22 Add text data processing
2022-05-22 Add more text to data section
2022-05-22 Add Grafana image, add citations
2022-05-23 Improve text and images
2022-05-23 Aplly correction from consultation
2022-05-23 Make code snippets smaller
2022-05-23 Beautify schematics in KiCad
2022-05-23 Inlcude schematics in text
2022-05-24 Add sleep_time to text, fix broken lstlisting
2022-05-25 Add case section, add data flow diagram
2022-05-26 Add script to find and replace space to non-breakable space, use it
2022-05-26 Add final PCB photos
2022-05-26 Cleanup citations, replace semestral work to bachelor
2022-05-26 Mirror 1.8V LDO in schematic, replaced in text
2022-05-26 Add BOM for PCBs, renew included schematic of mainBoard, start work at toc of attachments, add 3D models
2022-05-26 fw: Fix I2C communication for mainBoard v1.1 -> delay at boot for coltage stabilisation at sensors
2022-05-26 Fix text from consultation
2022-05-26 Add final chapter and grafana screenshots
2022-05-27 Replaced space chars with unbreakable spaces
2022-05-27 fw: add missing WIF_CHECKER to run task with MQTT
2022-05-27 Add info about used library in fw, add toc of electronical attachment
2022-05-27 Make links in citations clickable
2022-05-27 Remove citation links from table of images
2022-05-27 Run unbreakableSpace script once again
2022-05-29 Add final pjhoto of device
2022-06-09 Make presentation
2022-06-13 Final bachelor presentation
